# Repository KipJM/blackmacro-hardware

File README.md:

# BMacro V2

> # This project took me over _*300*_ hours of work to create.
> Donations to my Ko-Fi would be highly appreciated! It'll support me to continue updating my project and its firmware.
> 
> ### **You can support me at: https://kip.gay/support**

> Additionally, if you're perhaps interested in purchasing an assembled blackmacro keyboard, let me know in github issues!
> I'd love to see if it's possible to mass manufacture this thing to bring costs down.

A bluetooth-capable condensed macro keyboard with a motorized jog wheel, powered by a Raspberry Pi Pico 2W.

### This keyboard's jog wheel gives you smooth analog control over the Davinci Resolve playhead, which is only possible on this keyboard or the official Speed Editor.

Supports remappable keyboard input, smooth scrolling, MIDI input, or
driverless Davinci Resolve control through reverse-engineered HID emulation.

Each key is a hotswappable MX-style plateless switch with a reverse-mounted addressable RGB LED.
The 2u and 1.5u in/out clips/timeline keys also feature screw-mount stabilizers.

The jog wheel is driven by a FOC-controlled brushless DC motor and a magnetic angle encoder, allowing for user-definable
haptic feedback and buttery smooth scrolling when working through your video timeline.

**It costs ~180 USD to create one blackmacro keyboard if not using CNC.**

> #### This hardware is purpose-built for blackmacro-lib. For more information on the purpose of this device, see [blackmacro-lib](https://github.com/KipJM/blackmacro-lib).
> #### For the firmware of this device, see [blackmacro-firmware](https://github.com/KipJM/blackmacro-firmware).

> ### Name
> Help me pick a better name for this thing...

> You're looking at version 2. For V1 archive switch to branch v1.

# Why
Bmacro (or Blackmacro keyboard) is designed to be an open source, leaner, customizable, and more powerful alternative to the Davinci Resolve Speed Editor keyboard.

The original speed editor features keys that aren't remappable and is locked to the Davinci Resolve software, only some of its keys feaure single-color LEDs,
plus its jog wheel doesn't feature the mechanical clutch found on its bigger Editor Keyboard sibling. Bmacro improves on this in almost every way, then adding
additional knobs to expand its input capabilities! While it features less keys than the Speed Editor, each key is software remappable so you can have the inputs you actually need.
Inspired by the smartknob project, the jog wheel is replaced with a Field Oriented Controlled BLDC motor, not only allowing it to emulate a mechanical clutch, but also other [software-defined haptic feedback!](https://www.youtube.com/watch?v=J9192DfZplk)

Running the FOSS Blackmacro firmware, bmacro can not only fully emulate all features of the Speed Editor and interface with Davinci Resolve without the need for any drivers,
but it can also emulate other inputs, such as smooth scrolling, volume control, generic macropad, or MIDI input. Through the rotary encoder knob and the 0.91 inch OLED screen, you can switch between these modes.

# License
This project is licensed under the CERN Open Hardware Licence Version 2 - Weakly Reciprocal.

Copyright © KIP 2026.

**Any individual or corporate entity are strictly forbidden from training "generative AI" analytical neural networks (LLMs, etc.) on contents of this project.**

Selling fabricated hardware of this project as-is is strongly discouraged. Please reach out to me at [kip@kip.gay](mailto://kip@kip.gay).

# Features
- 21 MX-style south-facing hotswap sockets
- Fully addressable RGB backlight LED for each key
- 2 Alps-style rotary encoder with click input

- High fidelity jog dial powered by the MT6701 magnetic encoder, **accurate to 0.02 degrees**
- BLDC Motorized jog dial power by the TMC6300 motor driver, providing dynamic haptic feedback

- 6000mAh built-in battery, enough battery life for over 40 hours of **non-stop usage**
- Efficient power management
- Seamless power handoff when disconnecting/connecting USB

- **An actual power switch**
- USB-Type C input

- Sandwich-mount style case
- Cool PCB designs :)

- Powered by Raspberry Pi Pico 2W
- Original moddable firmware
- Native compatibility with Davinci Resolve (unofficial)
- Wide HID emulation capability, can also act as a mouse/keyboard/game controller/MIDI device
- Bluetooth & WLAN capable

# Folder Structure
This project is made up of two PCBs and a case. The PCB project and production files can be found inside each board's folder within PCB/. For Bill of Materials, please also see each board's respective bom/bom.csv.

# BOM
You can find a merged BOM of all parts at the root of this project, however for more info please see the board-specific BOMs. The master BOM might be incorrect.

Bill of materials are separated by boards, please see `bom.csv` within the the bom/ folder of each PCB. `Quantity` is the amount of that part used on this board, `Actual Total Cost` represent the amount I spent to satisfy the entire project's needs on that particular component, so it's influenced by my inventory, regional price differences, and discounts, so it should only serve as a rough estimate of how much the project's gonna cost you. If "-" is in place of the price entry, it means the price has already been listed elsewhere (or on another BOM).

Also note that any `LCSC #` values you find in the KiCAD project are likely incorrect!

3D printed part cost is calculated based on JLC3DP.

# Electronics
The project is made up of two boards:
- The dial board (aka the jog wheel board)
- The base board (aka the keyboard board)

Use each PCB's respective `{name}_bom.csv` for purchasing parts, I recommend using the interactive BOM HTML for part placement reference.

## Dial board

|                                                 |                                               |
|:-----------------------------------------------:|:---------------------------------------------:|
|    |    |
|  |  |

The motor driver, TMC6300, is only available in QFN packages. I recommend purchasing a stencil along with your PCB (at least get solder paste and flux).
You should get a cable along with your motor terminated on one side as a small JST male connector, you'll need to crimp a 3-pin JST EH connector on the other side.

Use standoffs and flathead (as in the head is flat) M2 screws to attach the motor to the PCB. The standoffs length is purposely chosen so the motor's builtin diametric magnet would be
perfectly aligned on top of the MT6701 magnetic encoder with the correct air gap. Unfortunately this means the push button functionality is not present, but you can
add this feature back by replacing the standoffs with stiff springs.

There are two solder jumpers letting you select how the motor controller chip should be activated. Use a soldering iron and a bit of solder, swipe right to bridge the connection, swipe left to break the connection. **You should only have one connected at a time.**
I recommend setting it to SIG, if set to 3V3, the motor driver will stay on as long as there's power, and the MCU cannot command it to go to sleep through the SIG pin.

## Base board

|                                                  |                                               |
|:------------------------------------------------:|:---------------------------------------------:|
|   |  |
|     |    |

The base board is designed for hotswap connectors, but the holes are plated so you technically can directly solder switches onto it.

> ## Make sure you're building the 11-2-fab2 or later versions of this board!
> 10-2-fab1, the initially fabricated version that I built this project on, includes a critical error with the logic shifter circuitry.
> If you built the 10-2-fab1 version, you'll have to remove the `C4` and `C5` capacitors and replace them with solder bridges, otherwise your LEDs won't work.

A few notable features of the base board:
- **The cutout:** the board is designed to work with a Pi Pico 2W. For the best Bluetooth performance,
the pcb is cut out under the pico's antenna.
- **Battery charging:** This board uses the HTP4056, a modified clone of the TP4056 that allows for a higher charging current.
- **USB**: The pico features three rectangular testpoints on the bottom for USB connections. To make this board hand solderable,
These TPs are connected through THTs. After soldering the pico to the board, fill the THTs with solder (use more than you would), then verify with a multimeter
that they have been soldered correctly. **This also means that the board is not full-SMT friendly. Beware!**
- **Stabilizers:** Screw-in stabilizers recommended. You'll need to get two 2U and one 3U steel wire.
- **Keycaps:** **16** 1U, **2** 1.5U, **2** 2U, **1** 3U.
- **MagEnc:** Most pins are unused. However, for extra rigidity terminate the other wires too!
- **Battery:** You'll have to terminate the battery leads into the JST connector. The top pin is unused.
- **Battery temperature probe:** For the NTC temperature probe, route its wires through the strain-relief so the leads
are inserted from the top of the board, and the probe should be at the bottom. Then tape the probe onto the battery with heat-resistant tape (safe at 40C min.)

I recommend fabbing the base PCB in white for better RGB LED performance. _(plus it just looks better)_

This board includes a 16-pin type-C port, DSBGA-9, and ESOP, which are hard to solder and requires a hotplate. I therefore recommend
getting partial PCBA for them and basic components.

When making the board interconnect cables, MAKE SURE the polarity is correct so that the correct pins are connected.
You can see silkscreen showing reference pins.

A stencil or hotplate is not required if you got partial PCBA, but flux/solder paste is highly recommended.

# 3D printed parts
Parts list:
- Case bottom
- Case top
- Plate
- (optional) jog wheel

> #### INFO!
> I do not recommmend printing the case, especially the plate, using PLA+ or regular PLA,
> It will sound very pingy!
>
> Instead, consider getting them fabricated using resin, laser-cut POM/Sheet metal, or CNC'd aluminium. 

# Case & Assembly

The case uses a sandwich-style mechanical keyboard mounting setup, with special modifications for the the jog wheel.

The `Assembly V2` Fusion 360 archive file contains all mounting details, including fasteners and heat-set inserts. Use
that as assembly reference.

### Switches
Should be the same as any mechanical keyboard. Search online for mech keyboard assembly guides.

### Heat-set Inserts, Standoffs, and Screws
This project uses two types of M2 screws, one type of M2 standoff, and one type of M2 heat-set inserts.

The specifications of each part is carefully chosen, make sure you get fasteners with the exact same specs.

### Battery
After taping the NTC temperature probe to the top side of the battery, apply double-sided foam tape
onto the battery compartment of the bottom case. Stick the battery onto the tape, and apply padding onto the compartment
walls if necessary.

### Assembly Order
After the heat-set inserts are installed, assemble the device in the following order:
1. I recommend driving the screws through the holes once before to drive out any excess support material.
2. Install screw-mounted stabs onto the PCB
3. Assemble all switches onto the plate
4. Tape the battery to the bottom case
5. install the dial board onto the case using standoffs
6. connect the pcb to the battery
7. preconnect all interconnect cables onto the dial board, leaving the base-side hanging.
8. snap the plate onto the pcb, install the pcb into the bottom case
9. connect all interconnect cables
10. screw in the four dial board mounting screws on the plate
11. install the OLED display
12. install the top case
13. screw in all six screws from the bottom, stop when the case is sealed shut.

### Sound
If printed out of PLA+, the keyboard will sound very pingy and hollow when assembled.
Fill the cavity in the case with foam, and consider doing tape/polyfil mods.

### Jog wheel
The jog wheel is designed to be CNC machined.
Use countersunk screws to install the dial onto the motor.

# The Motor
Unfortunately, there is no information on the manufacturer or datasheet of the motor used in this project. It seems to be from a leftover stock of motors that many small AliExpress vendors are reselling.

There should be a red ring at the bottom with three pin headers, two functionless 01x02 pins and one 01x03 UVW header. Make sure you're getting one that rotates 360 degrees with no limit mechanism.

The quality of the motor seems to vary, with some having low amounts of cogging, and some with none whatsoever. You may need to buy multiple to get one without cogging, but it's worth it (it's quite cheap anyways)!

The resellers use the same three images on their listings, lookup "2806 bldc" / "2806无刷电机" on AliExpress and you'll find a vendor.

# Firmware
Firmware is hosted at a separate repository. See https://github.com/KipJM/blackmacro-firmware.

# References
- https://github.com/shaise/DiSE
- https://github.com/scottbez1/smartknob
- https://github.com/dmcke5/Hapticpad

---

This project is not affiliated with or endorsed by Blackmagicdesign and Davinci Resolve.

Promo images rendered in Blender Cycles with openimagedenoise, please excuse any denoising artifacts. Yes the images are 8k and like 5mB, no I'm not sorry.

Davinci Resolve Compatibility is achieved through my project [blackmacro-lib](https://github.com/KipJM/blackmacro-lib).
It emulates a Speed Editor keyboard's HID protocols without decompilation of any blackmagic software/firmware.

Bmacro _(a.k.a. Blackmacro keyboard)_ is a fully original electronics hardware designed and fabricated by me, **KIP**. I am licensing this project under the CERN Open Hardware License Version 2 - Weakly Reciprocal. I reserve its copyright and the right to sell this hardware and its designs.

_Copyright © 2026_ **KIP**

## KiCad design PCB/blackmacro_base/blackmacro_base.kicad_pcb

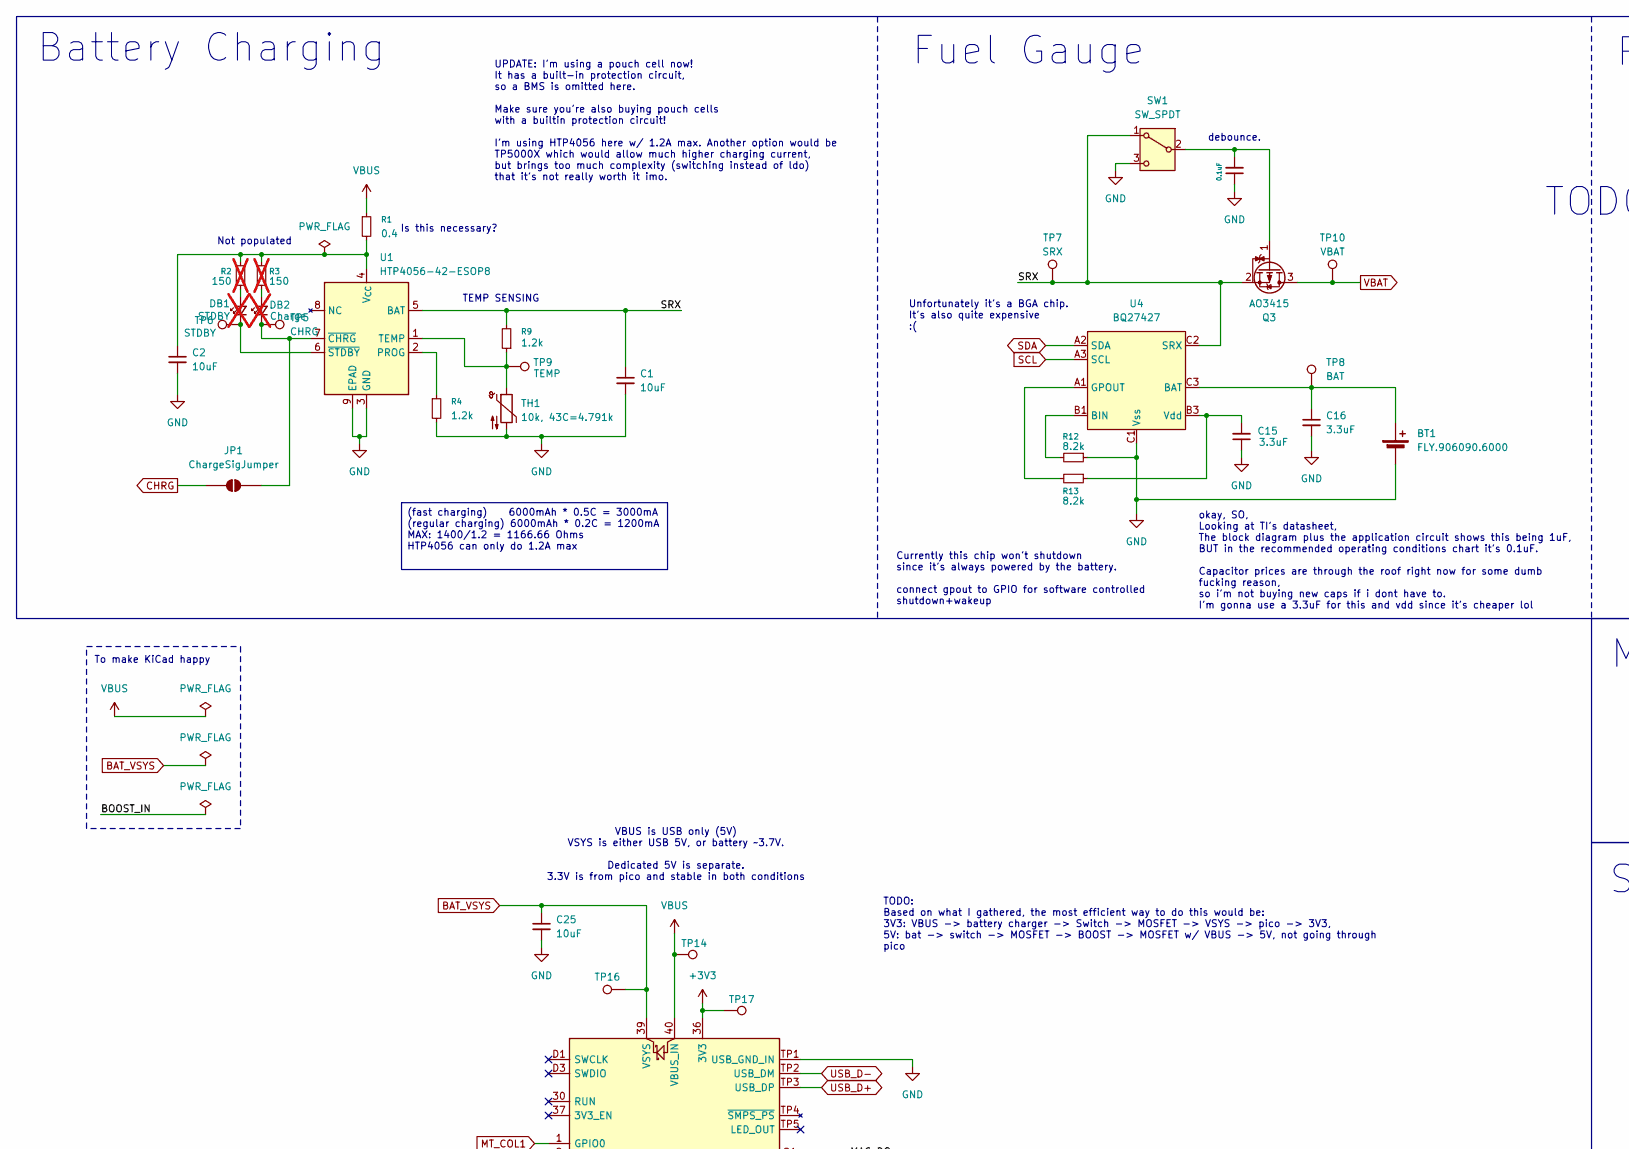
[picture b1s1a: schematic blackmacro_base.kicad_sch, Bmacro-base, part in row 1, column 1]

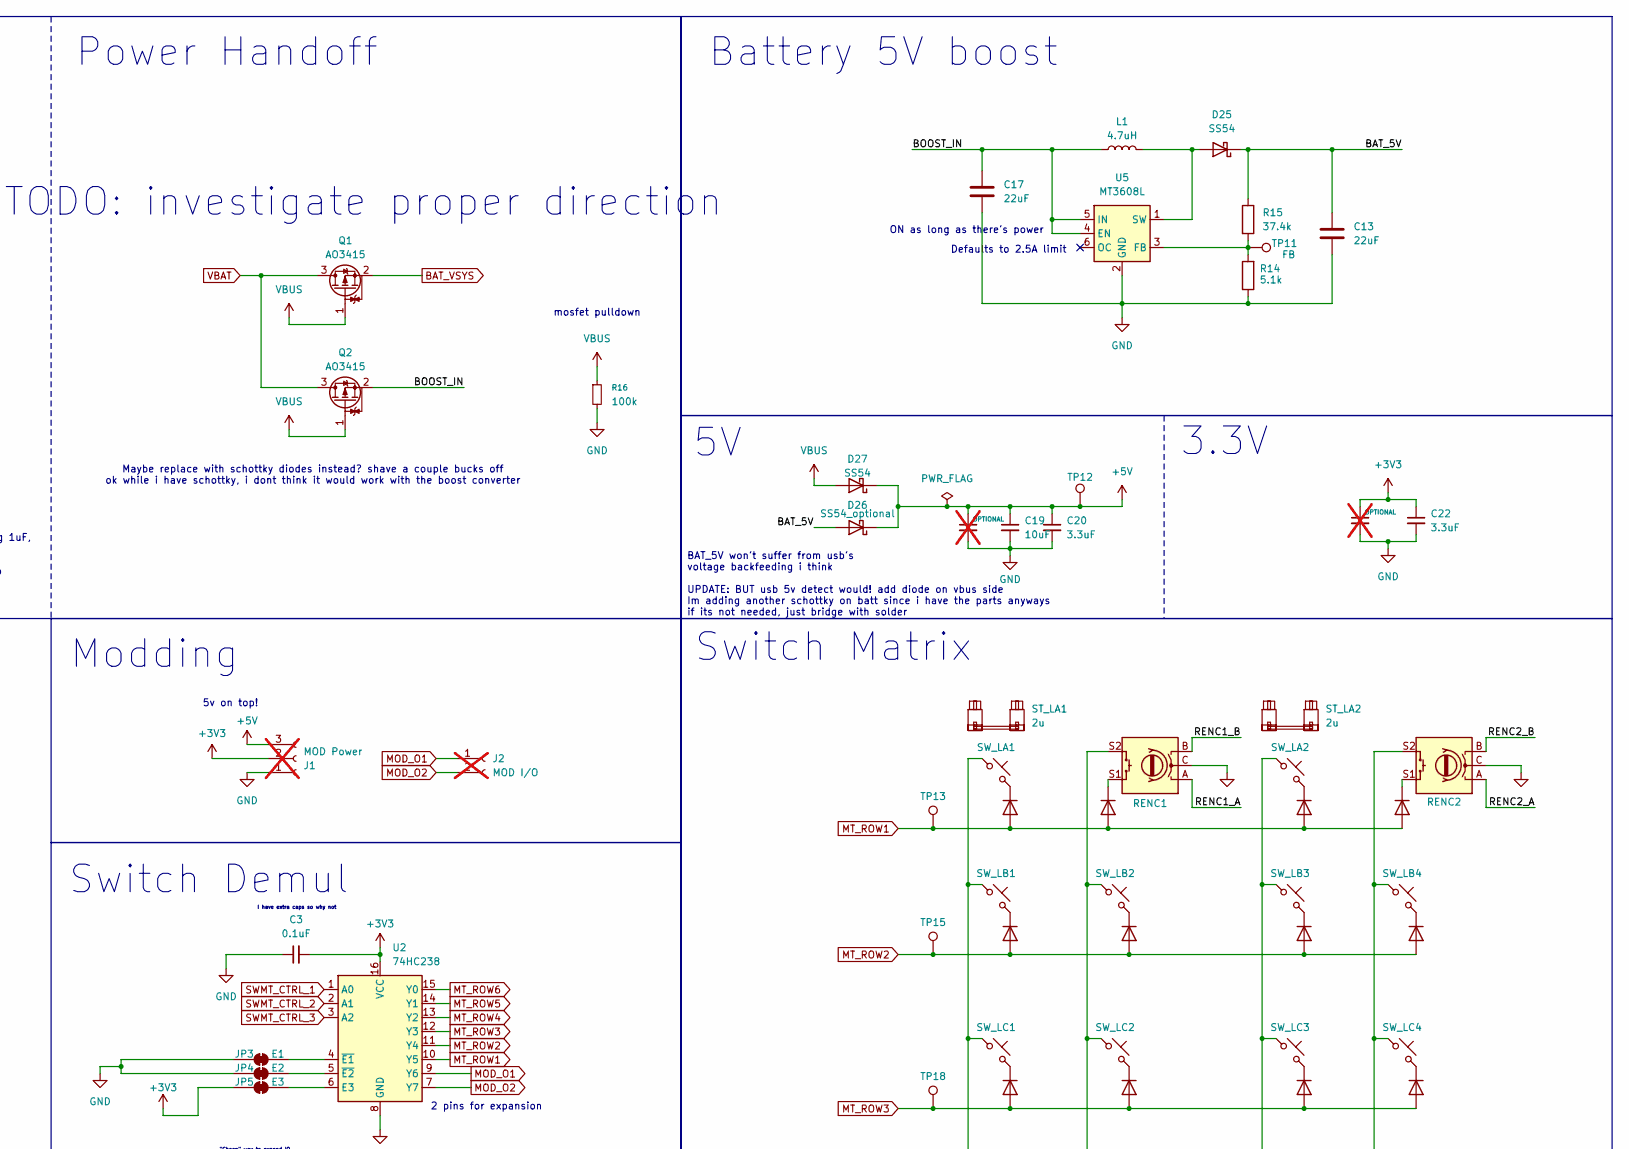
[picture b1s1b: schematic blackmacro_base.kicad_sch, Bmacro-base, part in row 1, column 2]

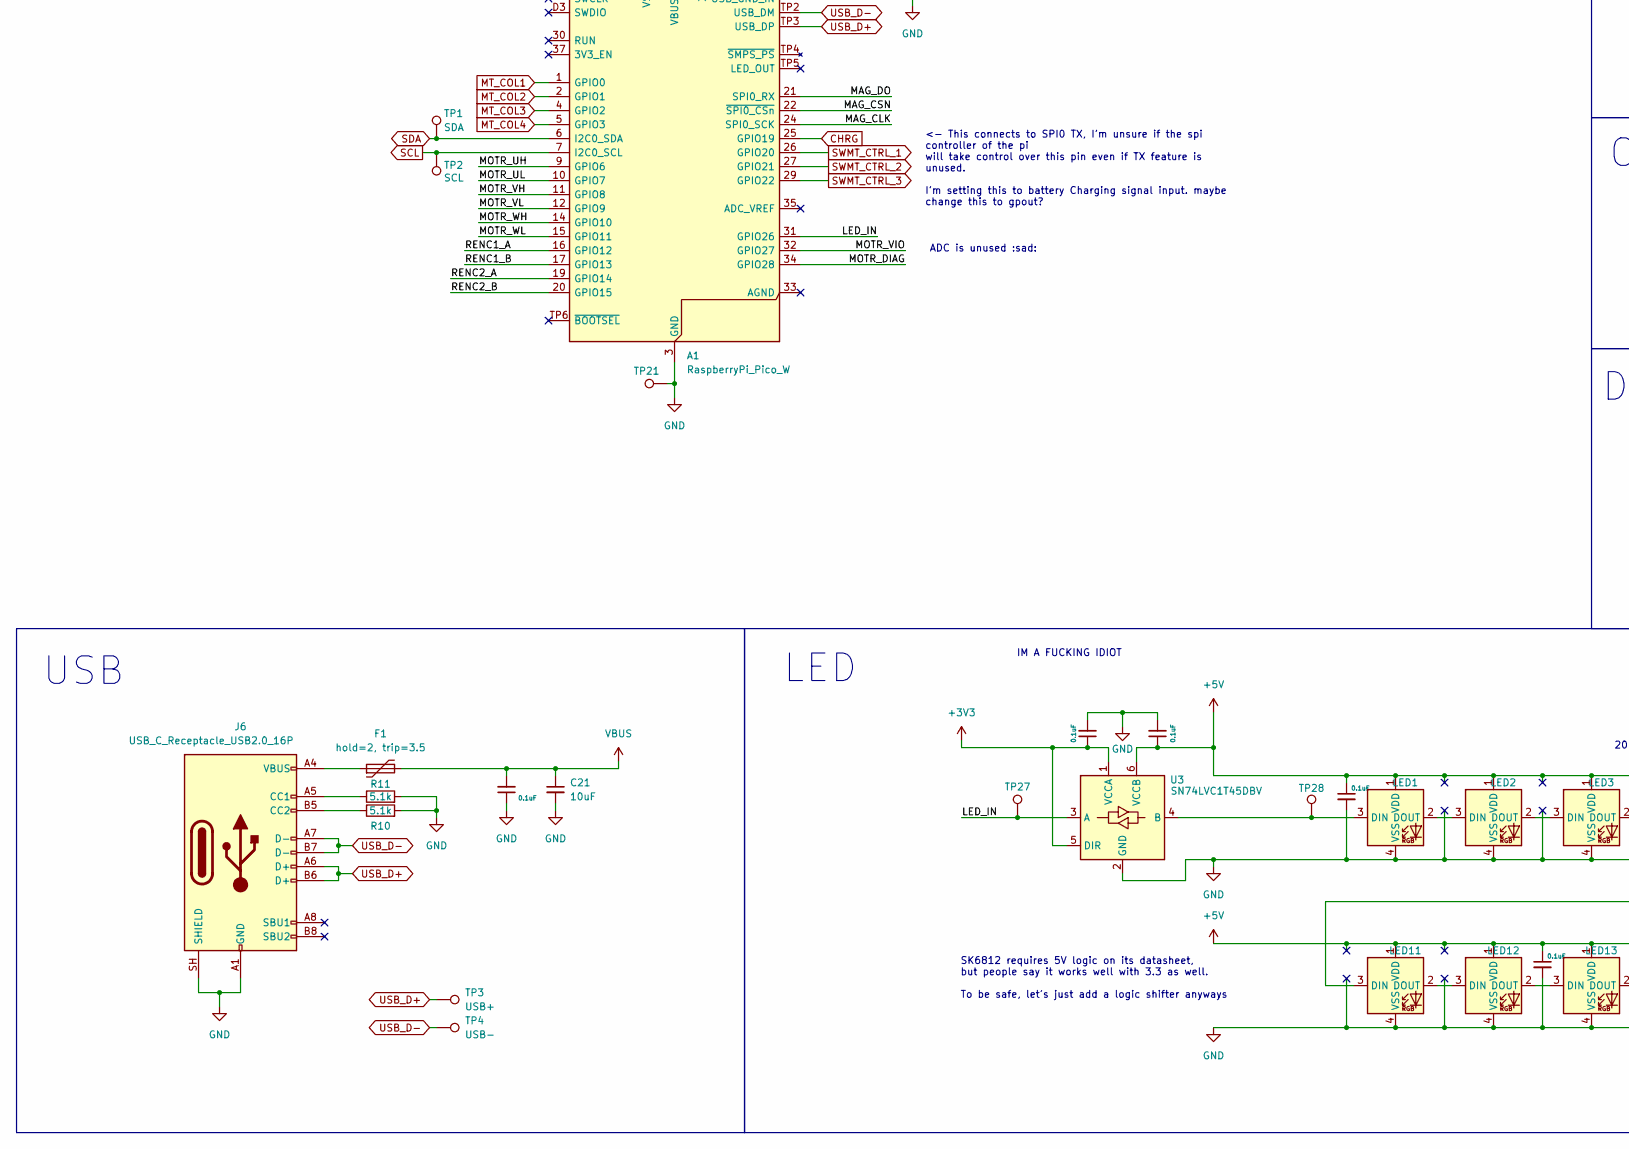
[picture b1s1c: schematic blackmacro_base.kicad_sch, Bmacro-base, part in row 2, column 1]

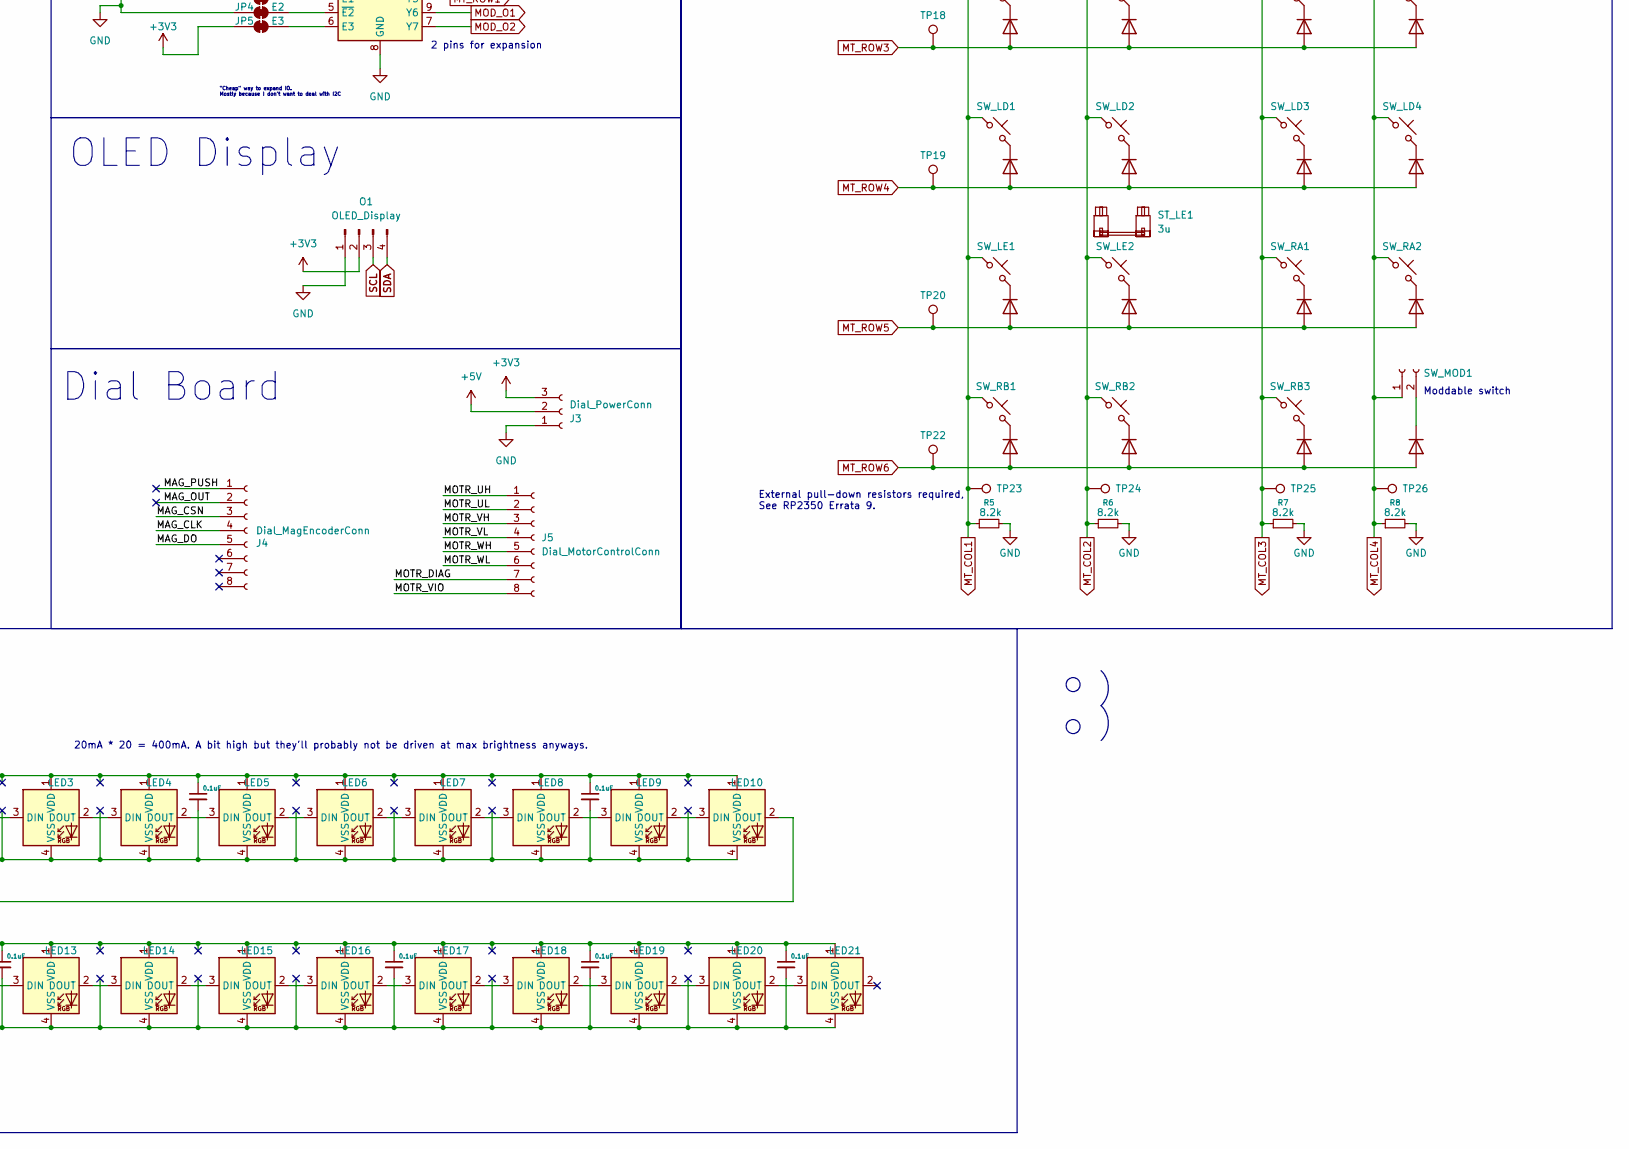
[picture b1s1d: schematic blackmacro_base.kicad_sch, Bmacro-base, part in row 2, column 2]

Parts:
A1: RaspberryPi_Pico_W; RaspberryPi_Pico_W_SMD_THTdebug
BT1: FLY.906090.6000; JST_EH_S3B-EH_1x03_P2.50mm_Horizontal
C1, C2, C19, C21, C25: 10uF; C_0603_1608Metric_Pad1.08x0.95mm_HandSolder
C3, C4, C5, C6, C7, C8, C9, C10, C11, C12, C14, C18: 0.1uF; C_1206_3216Metric_Pad1.33x1.80mm_HandSolder
C13, C17: 22uF; C_0603_1608Metric_Pad1.08x0.95mm_HandSolder
C15, C16, C20, C22: 3.3uF; C_0603_1608Metric_Pad1.08x0.95mm_HandSolder
C23, C24: OPTIONAL; C_1206_3216Metric_Pad1.33x1.80mm_HandSolder; not fitted
D1, D2, D3, D4, D5, D6, D7, D8, D9, D10, D11, D12, D13, D14, D15, D16, D17, D18, D19, D20, D21, D22, D23, D24: 1N4148WS; D_DO-35_SOD27_P7.62mm_Horizontal
D25, D27: SS54; D_SMA_Handsoldering
D26: SS54_optional; D_SMA_Handsoldering
DB1: STDBY; LED_0603_1608Metric_Pad1.05x0.95mm_HandSolder; not fitted
DB2: Charge; LED_0603_1608Metric_Pad1.05x0.95mm_HandSolder; not fitted
F1: hold=2, trip=3.5; Fuse_1206_3216Metric_Pad1.42x1.75mm_HandSolder
J1: MOD Power; PinSocket_1x03_P2.54mm_Horizontal; not fitted
J2: MOD I/O; PinSocket_1x02_P2.54mm_Horizontal; not fitted
J3: Dial_PowerConn; JST_EH_S3B-EH_1x03_P2.50mm_Horizontal
J4: Dial_MagEncoderConn; JST_PH_S8B-PH-K_1x08_P2.00mm_Horizontal
J5: Dial_MotorControlConn; JST_PH_S8B-PH-K_1x08_P2.00mm_Horizontal
J6: USB_C_Receptacle_USB2.0_16P; USB_C_Receptacle_HCTL_HC-TYPE-C-16P-01A
JP1: ChargeSigJumper; SolderJumper-2_P1.3mm_Open_TrianglePad1.0x1.5mm
JP3: E1; SolderJumper-2_P1.3mm_Bridged_RoundedPad1.0x1.5mm
JP4: E2; SolderJumper-2_P1.3mm_Bridged_RoundedPad1.0x1.5mm
JP5: E3; SolderJumper-2_P1.3mm_Bridged_RoundedPad1.0x1.5mm
L1: 4.7uH; L_Changjiang_FXL0630
LED1, LED2, LED3, LED4, LED5, LED6, LED7, LED8, LED9, LED10, LED11, LED12, LED13, LED14, LED15, LED16, LED17, LED18, LED19, LED20, LED21: SK6812MINI-E; LED_MX_6028R
O1: OLED_Display; PinHeader_1x04_P2.54mm_Vertical
Q1, Q2, Q3: AO3415; SOT-23_Handsoldering
R1: 0.4; R_2512_6332Metric_Pad1.40x3.35mm_HandSolder
R2, R3: 150; R_0603_1608Metric_Pad0.98x0.95mm_HandSolder; not fitted
R4, R9: 1.2k; R_0805_2012Metric_Pad1.20x1.40mm_HandSolder
R5, R6, R7, R8, R12, R13: 8.2k; R_0805_2012Metric_Pad1.20x1.40mm_HandSolder
R10, R11, R14: 5.1k; R_0603_1608Metric_Pad0.98x0.95mm_HandSolder
R15: 37.4k; R_0603_1608Metric_Pad0.98x0.95mm_HandSolder
R16: 100k; R_0603_1608Metric_Pad0.98x0.95mm_HandSolder
RENC1, RENC2: RotaryEncoder_Switch; RotaryEncoder_Alps_EC11E-Switch_Vertical_H20mm
ST_LA1, ST_LA2: 2u; STAB_MX_2u
ST_LE1: 3u; STAB_MX_3u
SW1: SW_SPDT; SW_SPDT_Shouhan_MSK12C02
SW_LA1, SW_LA2: SW_Push_45deg; SW_Hotswap_Kailh_MX_Plated_2.00u
SW_LB1, SW_LB2, SW_LB3, SW_LB4: SW_Push_45deg; SW_Hotswap_Kailh_MX_Plated_1.00u
SW_LC1, SW_LC2, SW_LC3, SW_LC4: SW_Push_45deg; SW_Hotswap_Kailh_MX_Plated_1.00u
SW_LD1, SW_LD2, SW_LD3, SW_LD4: SW_Push_45deg; SW_Hotswap_Kailh_MX_Plated_1.00u
SW_LE1: SW_Push_45deg; SW_Hotswap_Kailh_MX_Plated_1.00u
SW_LE2: SW_Push_45deg; SW_Hotswap_Kailh_MX_Plated_3.00u
SW_MOD1: Conn_01x02_Socket; SolderWire-0.127sqmm_1x02_P3.7mm_D0.48mm_OD1mm
SW_RA1, SW_RA2: SW_Push_45deg; SW_Hotswap_Kailh_MX_Plated_1.50u
SW_RB1, SW_RB2, SW_RB3: SW_Push_45deg; SW_Hotswap_Kailh_MX_Plated_1.00u
TH1: 10k, 43C=4.791k; SolderWire-0.127sqmm_1x02_P3.7mm_D0.48mm_OD1mm_Relief
TP1: SDA; TestPoint_THTPad_D1.5mm_Drill0.7mm
TP2: SCL; TestPoint_THTPad_D1.5mm_Drill0.7mm
TP3: USB+; TestPoint_Pad_D1.5mm
TP4: USB-; TestPoint_Pad_D1.5mm
TP5: CHRG; TestPoint_Pad_D1.5mm
TP6: STDBY; TestPoint_Pad_D1.5mm
TP7: SRX; TestPoint_THTPad_D1.5mm_Drill0.7mm
TP8: BAT; TestPoint_THTPad_D1.5mm_Drill0.7mm
TP9: TEMP; TestPoint_Pad_D1.5mm
TP10: VBAT; TestPoint_THTPad_D1.5mm_Drill0.7mm
TP11: FB; TestPoint_Pad_D1.0mm
TP12: 5V; TestPoint_THTPad_D1.5mm_Drill0.7mm
TP13: KROW1; TestPoint_Pad_D1.0mm
TP14: VBUS; TestPoint_THTPad_D1.5mm_Drill0.7mm
TP15: KROW2; TestPoint_Pad_D1.0mm
TP16: VSYS; TestPoint_Pad_D1.5mm
TP17: 3V3; TestPoint_THTPad_D1.5mm_Drill0.7mm
TP18: KROW3; TestPoint_Pad_D1.0mm
TP19: KROW4; TestPoint_Pad_D1.0mm
TP20: KROW5; TestPoint_Pad_D1.0mm
TP21: GND; TestPoint_THTPad_D1.5mm_Drill0.7mm
TP22: KROW6; TestPoint_Pad_D1.0mm
TP23: KCOL1; TestPoint_Pad_D1.0mm
TP24: KCOL2; TestPoint_Pad_D1.0mm
TP25: KCOL3; TestPoint_Pad_D1.0mm
TP26: KCOL4; TestPoint_Pad_D1.0mm
TP27: LED1; TestPoint_Pad_D1.5mm
TP28: LED2; TestPoint_Pad_D1.5mm
U1: HTP4056-42-ESOP8; SOIC-8-1EP_3.9x4.9mm_P1.27mm_EP2.41x3.3mm_ThermalVias
U2: 74HC238; SOIC-16_3.9x9.9mm_P1.27mm
U3: SN74LVC1T45DBV; SOT-23-6_Handsoldering
U4: BQ27427; Texas_DSBGA-9_1.62x1.58mm_Layout3x3_P0.5mm
U5: MT3608L; SOT-23-6_Handsoldering

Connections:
+3V3: A1.36 (3V3), C3.2, C5.1, C22.1, C23.1, J1.2, J3.3, JP5.1 (A), O1.2, TP17.1 (1_1), U2.16 (VCC), U3.1 (VCCA), U3.5 (DIR)
+5V: C4.1, C6.1, C7.1, C8.1, C9.1, C10.1, C11.1, C12.1, C19.1, C20.1, C24.1, D26.1 (K), D27.1 (K), J1.3, J3.2, LED1.1 (VDD), LED2.1 (VDD), LED3.1 (VDD), LED4.1 (VDD), LED5.1 (VDD), LED6.1 (VDD), LED7.1 (VDD), LED8.1 (VDD), LED9.1 (VDD), LED10.1 (VDD), LED11.1 (VDD), LED12.1 (VDD), LED13.1 (VDD), LED14.1 (VDD), LED15.1 (VDD), LED16.1 (VDD), LED17.1 (VDD), LED18.1 (VDD), LED19.1 (VDD), LED20.1 (VDD), LED21.1 (VDD), TP12.1 (1_1), U3.6 (VCCB)
/BAT_5V: C13.1, D25.1 (K), D26.2 (A), R15.1
/BOOST_IN: C17.1, L1.1, Q2.2 (S), U5.4 (EN), U5.5 (IN)
/LED_IN: A1.31 (GPIO26), TP27.1 (1_1), U3.3 (A)
/MAG_CLK: A1.24 (SPI0_SCK), J4.4
/MAG_CSN: A1.22 (~SPI0_CSn), J4.3
/MAG_DO: A1.21 (SPI0_RX), J4.5
/MAG_OUT: J4.2
/MAG_PUSH: J4.1
/MOTR_DIAG: A1.34 (GPIO28), J5.7
/MOTR_UH: A1.9 (GPIO6), J5.1
/MOTR_UL: A1.10 (GPIO7), J5.2
/MOTR_VH: A1.11 (GPIO8), J5.3
/MOTR_VIO: A1.32 (GPIO27), J5.8
/MOTR_VL: A1.12 (GPIO9), J5.4
/MOTR_WH: A1.14 (GPIO10), J5.5
/MOTR_WL: A1.15 (GPIO11), J5.6
/RENC1_A: A1.16 (GPIO12), RENC1.A
/RENC1_B: A1.17 (GPIO13), RENC1.B
/RENC2_A: A1.19 (GPIO14), RENC2.A
/RENC2_B: A1.20 (GPIO15), RENC2.B
/SRX: C1.1, Q3.2 (S), R9.2, SW1.1 (A), TP7.1 (1_1), U1.5 (BAT), U4.C2 (SRX)
BAT_VSYS: A1.39 (VSYS), C25.1, Q1.2 (S), TP16.1 (1_1)
CHRG: A1.25 (GPIO19), JP1.2 (B)
GND: A1.3 (GND), A1.8 (GND), A1.13 (GND), A1.18 (GND), A1.23 (GND), A1.28 (GND), A1.38 (GND), A1.D2 (GND), A1.TP1 (USB_GND_IN), BT1.2 (-), C1.2, C2.2, C3.1, C4.2, C5.2, C6.2, C7.2, C8.2, C9.2, C10.2, C11.2, C12.2, C13.2, C14.1, C15.1, C16.2, C17.2, C18.1, C19.2, C20.2, C21.2, C22.2, C23.2, C24.2, C25.2, J1.1, J3.1, J6.A1 (GND), J6.A12 (GND), J6.B1 (GND), J6.B12 (GND), J6.SH (SHIELD), JP3.1 (A), JP4.1 (A), LED1.4 (VSS), LED2.4 (VSS), LED3.4 (VSS), LED4.4 (VSS), LED5.4 (VSS), LED6.4 (VSS), LED7.4 (VSS), LED8.4 (VSS), LED9.4 (VSS), LED10.4 (VSS), LED11.4 (VSS), LED12.4 (VSS), LED13.4 (VSS), LED14.4 (VSS), LED15.4 (VSS), LED16.4 (VSS), LED17.4 (VSS), LED18.4 (VSS), LED19.4 (VSS), LED20.4 (VSS), LED21.4 (VSS), O1.1, R4.2, R5.2, R6.2, R7.2, R8.2, R10.2, R11.2, R12.1, R14.1, R16.2, RENC1.C, RENC2.C, SW1.3 (C), TH1.2, TP21.1 (1_1), U1.3 (GND), U1.9 (EPAD), U2.8 (GND), U3.2 (GND), U4.B2 (Vss), U4.C1 (Vss), U5.2 (GND)
MOD_O1: J2.1, U2.9 (Y6)
MOD_O2: J2.2, U2.7 (Y7)
MT_COL1: A1.1 (GPIO0), R5.1, SW_LA1.1, SW_LB1.1, SW_LC1.1, SW_LD1.1, SW_LE1.1, SW_RB1.1, TP23.1 (1_1)
MT_COL2: A1.2 (GPIO1), R6.1, RENC1.S2, SW_LB2.1, SW_LC2.1, SW_LD2.1, SW_LE2.1, SW_RB2.1, TP24.1 (1_1)
MT_COL3: A1.4 (GPIO2), R7.1, SW_LA2.1, SW_LB3.1, SW_LC3.1, SW_LD3.1, SW_RA1.1, SW_RB3.1, TP25.1 (1_1)
MT_COL4: A1.5 (GPIO3), R8.1, RENC2.S2, SW_LB4.1, SW_LC4.1, SW_LD4.1, SW_MOD1.1, SW_RA2.1, TP26.1 (1_1)
MT_ROW1: D1.2 (A), D2.2 (A), D3.2 (A), D4.2 (A), TP13.1 (1_1), U2.10 (Y5)
MT_ROW2: D5.2 (A), D6.2 (A), D7.2 (A), D8.2 (A), TP15.1 (1_1), U2.11 (Y4)
MT_ROW3: D9.2 (A), D10.2 (A), D11.2 (A), D12.2 (A), TP18.1 (1_1), U2.12 (Y3)
MT_ROW4: D13.2 (A), D14.2 (A), D15.2 (A), D16.2 (A), TP19.1 (1_1), U2.13 (Y2)
MT_ROW5: D17.2 (A), D18.2 (A), D19.2 (A), D20.2 (A), TP20.1 (1_1), U2.14 (Y1)
MT_ROW6: D21.2 (A), D22.2 (A), D23.2 (A), D24.2 (A), TP22.1 (1_1), U2.15 (Y0)
unnamed: BT1.1 (+), C16.1, TP8.1 (1_1), U4.C3 (BAT)
unnamed: D1.1 (K), SW_LA1.2
unnamed: D2.1 (K), SW_LA2.2
unnamed: D3.1 (K), RENC1.S1
unnamed: D4.1 (K), RENC2.S1
unnamed: D5.1 (K), SW_LB1.2
unnamed: D6.1 (K), SW_LB2.2
unnamed: D7.1 (K), SW_LB3.2
unnamed: D8.1 (K), SW_LB4.2
unnamed: D9.1 (K), SW_LC1.2
unnamed: D10.1 (K), SW_LC2.2
unnamed: D11.1 (K), SW_LC3.2
unnamed: D12.1 (K), SW_LC4.2
unnamed: D13.1 (K), SW_LD1.2
unnamed: D14.1 (K), SW_LD2.2
unnamed: D15.1 (K), SW_LD3.2
unnamed: D16.1 (K), SW_LD4.2
unnamed: D17.1 (K), SW_LE1.2
unnamed: D18.1 (K), SW_LE2.2
unnamed: D19.1 (K), SW_RA1.2
unnamed: D20.1 (K), SW_RA2.2
unnamed: D21.1 (K), SW_RB1.2
unnamed: D22.1 (K), SW_RB2.2
unnamed: D23.1 (K), SW_RB3.2
unnamed: D24.1 (K), SW_MOD1.2
unnamed: D25.2 (A), L1.2, U5.1 (SW)
unnamed: DB1.2 (A), R2.2
unnamed: DB1.1 (K), TP6.1 (1_1), U1.6 (~STDBY)
unnamed: DB2.2 (A), R3.2
unnamed: DB2.1 (K), JP1.1 (A), TP5.1 (1_1), U1.7 (~CHRG)
unnamed: F1.1, J6.A4 (VBUS), J6.A9 (VBUS), J6.B4 (VBUS), J6.B9 (VBUS)
unnamed: J6.A5 (CC1), R11.1
unnamed: J6.B5 (CC2), R10.1
unnamed: JP3.2 (B), U2.4 (~E1)
unnamed: JP4.2 (B), U2.5 (~E2)
unnamed: JP5.2 (B), U2.6 (E3)
unnamed: LED1.3 (DIN), TP28.1 (1_1), U3.4 (B)
unnamed: LED1.2 (DOUT), LED2.3 (DIN)
unnamed: LED2.2 (DOUT), LED3.3 (DIN)
unnamed: LED3.2 (DOUT), LED4.3 (DIN)
unnamed: LED4.2 (DOUT), LED5.3 (DIN)
unnamed: LED5.2 (DOUT), LED6.3 (DIN)
unnamed: LED6.2 (DOUT), LED7.3 (DIN)
unnamed: LED7.2 (DOUT), LED8.3 (DIN)
unnamed: LED8.2 (DOUT), LED9.3 (DIN)
unnamed: LED9.2 (DOUT), LED10.3 (DIN)
unnamed: LED10.2 (DOUT), LED11.3 (DIN)
unnamed: LED11.2 (DOUT), LED12.3 (DIN)
unnamed: LED12.2 (DOUT), LED13.3 (DIN)
unnamed: LED13.2 (DOUT), LED14.3 (DIN)
unnamed: LED14.2 (DOUT), LED15.3 (DIN)
unnamed: LED15.2 (DOUT), LED16.3 (DIN)
unnamed: LED16.2 (DOUT), LED17.3 (DIN)
unnamed: LED17.2 (DOUT), LED18.3 (DIN)
unnamed: LED18.2 (DOUT), LED19.3 (DIN)
unnamed: LED19.2 (DOUT), LED20.3 (DIN)
unnamed: LED20.2 (DOUT), LED21.3 (DIN)
unnamed: C14.2, Q3.1 (G), SW1.2 (B)
unnamed: R4.1, U1.2 (PROG)
unnamed: R9.1, TH1.1, TP9.1 (1_1), U1.1 (TEMP)
unnamed: C2.1, R1.2, R2.1, R3.1, U1.4 (V_{CC})
unnamed: R12.2, U4.B1 (BIN)
unnamed: R13.2, U4.A1 (GPOUT)
unnamed: C15.2, R13.1, U4.B3 (Vdd)
unnamed: R14.2, R15.2, TP11.1 (1_1), U5.3 (FB)
SCL: A1.7 (I2C0_SCL), O1.3, TP2.1 (1_1), U4.A3 (SCL)
SDA: A1.6 (I2C0_SDA), O1.4, TP1.1 (1_1), U4.A2 (SDA)
SWMT_CTRL_1: A1.26 (GPIO20), U2.1 (A0)
SWMT_CTRL_2: A1.27 (GPIO21), U2.2 (A1)
SWMT_CTRL_3: A1.29 (GPIO22), U2.3 (A2)
USB_D+: A1.TP3 (USB_DP), J6.A6 (D+), J6.B6 (D+), TP3.1 (1_1)
USB_D-: A1.TP2 (USB_DM), J6.A7 (D-), J6.B7 (D-), TP4.1 (1_1)
VBAT: Q1.3 (D), Q2.3 (D), Q3.3 (D), TP10.1 (1_1)
VBUS: A1.40 (VBUS_IN), C18.2, C21.1, D27.2 (A), F1.2, Q1.1 (G), Q2.1 (G), R1.1, R16.1, TP14.1 (1_1)

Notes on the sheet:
Dial Board
SK6812 requires 5V logic on its datasheet, but people say it works well with 3.3 as well. To be safe, let's just add a logic shifter anyways
3.3V
Battery Charging
Fuel Gauge
TEMP SENSING
5v on top!
mosfet pulldown
Battery 5V boost
TODO: investigate proper direction
Defaults to 2.5A limit
"Cheap" way to expand IO. Mostly because I don't want to deal with I2C
VBUS is USB only (5V) VSYS is either USB 5V, or battery ~3.7V. Dedicated 5V is separate. 3.3V is from pico and stable in both conditions
Currently this chip won't shutdown since it's always powered by the battery. connect gpout to GPIO for software controlled shutdown+wakeup
Power Handoff
BAT_5V won't suffer from usb's voltage backfeeding i think UPDATE: BUT usb 5v detect would! add diode on vbus side Im adding another schottky on batt since i have the parts anyways if its not needed, just bridge with solder
USB
Switch Matrix
OLED Display
To make KiCad happy
2 pins for expansion
Switch Demul
debounce.
External pull-down resistors required, See RP2350 Errata 9.
ON as long as there's power
Is this necessary?
Not populated
LED
okay, SO, Looking at TI's datasheet, The block diagram plus the application circuit shows this being 1uF, BUT in the recommended operating conditions chart it's 0.1uF. Capacitor prices are through the roof right now for some dumb fucking reason, so i'm not buying new caps if i dont have to. I'm gon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
IM A FUCKING IDIOT
Maybe replace with schottky diodes instead? shave a couple bucks off ok while i have schottky, i dont think it would work with the boost converter
I have extra caps so why not
Unfortunately it's a BGA chip. It's also quite expensive :(
UPDATE: I'm using a pouch cell now! It has a built-in protection circuit, so a BMS is omitted here. Make sure you're also buying pouch cells with a builtin protection circuit! I'm using HTP4056 here w/ 1.2A max. Another option would be TP5000X which would allow much higher charging current, but bri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
Modding
20mA * 20 = 400mA. A bit high but they'll probably not be driven at max brightness anyways.
Moddable switch
ADC is unused :sad:
TODO: Based on what I gathered, the most efficient way to do this would be: 3V3: VBUS -> battery charger -> Switch -> MOSFET -> VSYS -> pico -> 3V3, 5V: bat -> switch -> MOSFET -> BOOST -> MOSFET w/ VBUS -> 5V, not going through pico
(fast charging) 6000mAh * 0.5C = 3000mA (regular charging) 6000mAh * 0.2C = 1200mA MAX: 1400/1.2 = 1166.66 Ohms HTP4056 can only do 1.2A max

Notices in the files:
PCB/blackmacro_dial/blackmacro_dial.kicad_pcb:
Copyright (c) 2026
